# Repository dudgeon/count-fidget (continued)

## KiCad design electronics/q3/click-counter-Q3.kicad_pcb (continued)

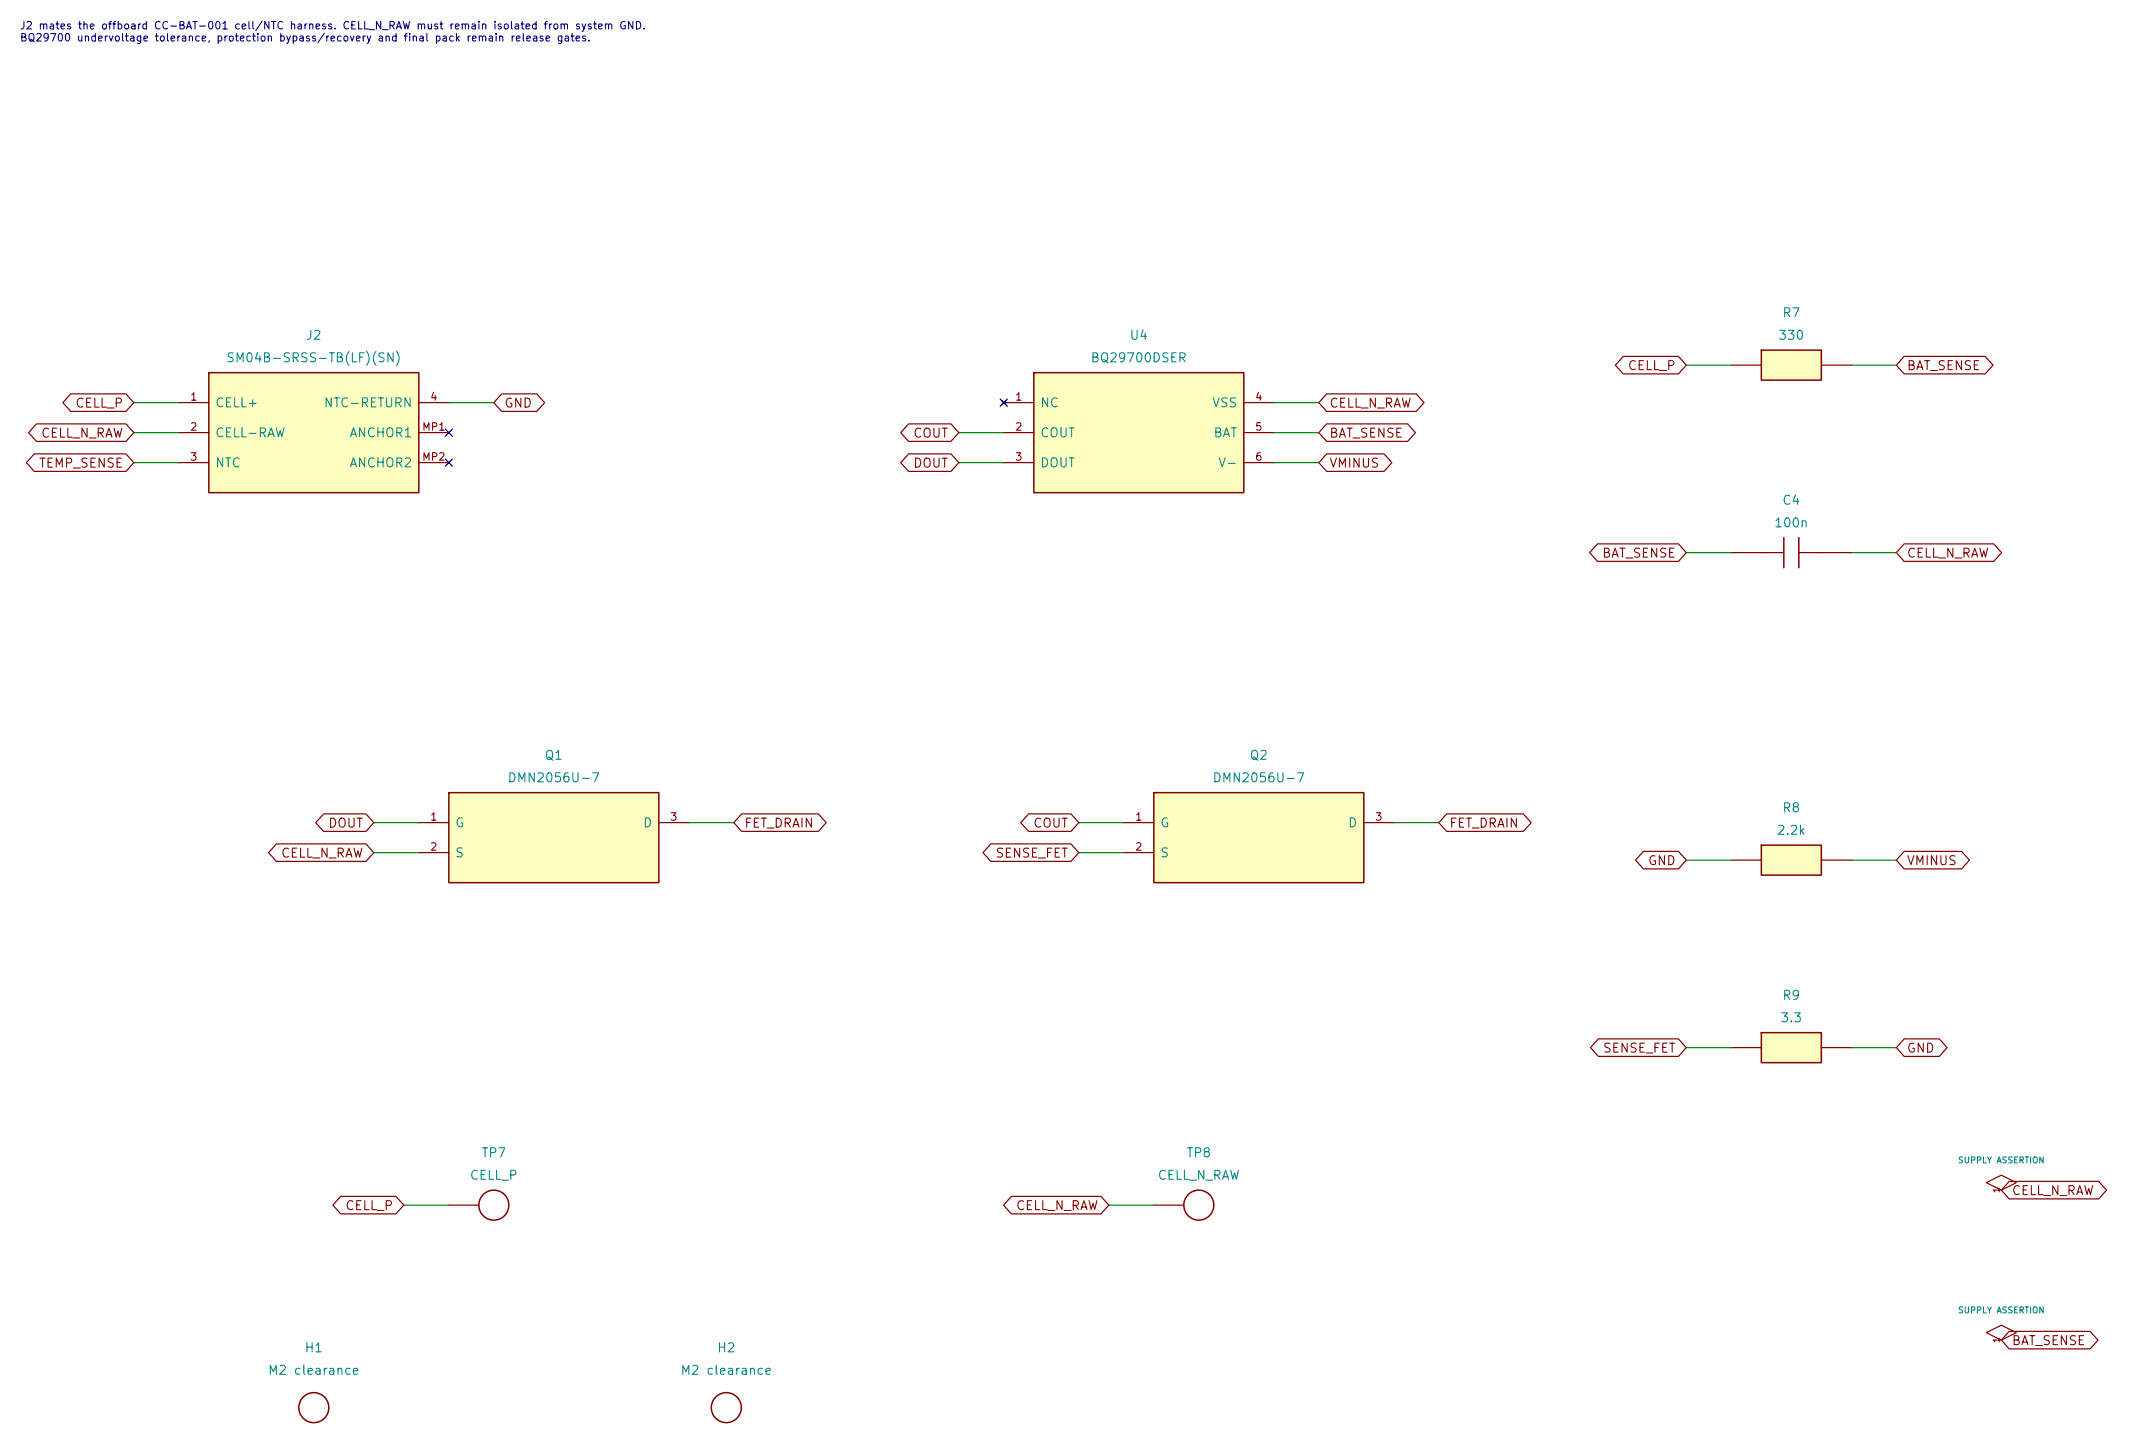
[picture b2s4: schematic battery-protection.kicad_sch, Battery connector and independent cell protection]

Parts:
C4: 100n; Capacitor_SMD_C_0603_1608Metric; MPN GRM188R71H104KA93D
H1, H2: M2 clearance; MountingHole_MountingHole_2.2mm_M2; MPN NPTH
J2: Battery + NTC; Connector_JST_JST_SH_SM04B-SRSS-TB_1x04-1MP_P1.00mm_Horizon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; MPN SM04B-SRSS-TB(LF)(SN)
Q1: Discharge FET; Package_TO_SOT_SMD_SOT-23; MPN DMN2056U-7
Q2: Charge FET; Package_TO_SOT_SMD_SOT-23; MPN DMN2056U-7
R7: 330; Resistor_SMD_R_0603_1608Metric; MPN RC0603FR-07330RL
R8: 2.2k; Resistor_SMD_R_0603_1608Metric; MPN RC0603FR-072K2L
R9: 3.3; Resistor_SMD_R_0603_1608Metric; MPN 0603WAF330KT5E
TP7: CELL_P; TestPoint_TestPoint_Pad_D1.5mm; MPN PCB LAND
TP8: CELL_N_RAW; TestPoint_TestPoint_Pad_D1.5mm; MPN PCB LAND
U4: Cell protector; Package_SON_WSON-6_1.5x1.5mm_P0.5mm; MPN BQ29700DSER

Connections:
BAT_SENSE: C4.1, R7.2, U4.5 (BAT)
CELL_N_RAW: C4.2, J2.2 (CELL-RAW), Q1.2 (S), TP8.1 (1_1), U4.4 (VSS)
CELL_P: J2.1 (CELL+), R7.1, TP7.1 (1_1); also elsewhere on the board
COUT: Q2.1 (G), U4.2 (COUT)
DOUT: Q1.1 (G), U4.3 (DOUT)
FET_DRAIN: Q1.3 (D), Q2.3 (D)
GND: J2.4 (NTC-RETURN), R8.1, R9.2; also elsewhere on the board
SENSE_FET: Q2.2 (S), R9.1
TEMP_SENSE: J2.3 (NTC); also elsewhere on the board
VMINUS: R8.2, U4.6 (V-)

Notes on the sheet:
J2 mates the offboard CC-BAT-001 cell/NTC harness. CELL_N_RAW must remain isolated from system GND. BQ29700 undervoltage tolerance, protection bypass/recovery and final pack remain release gates.

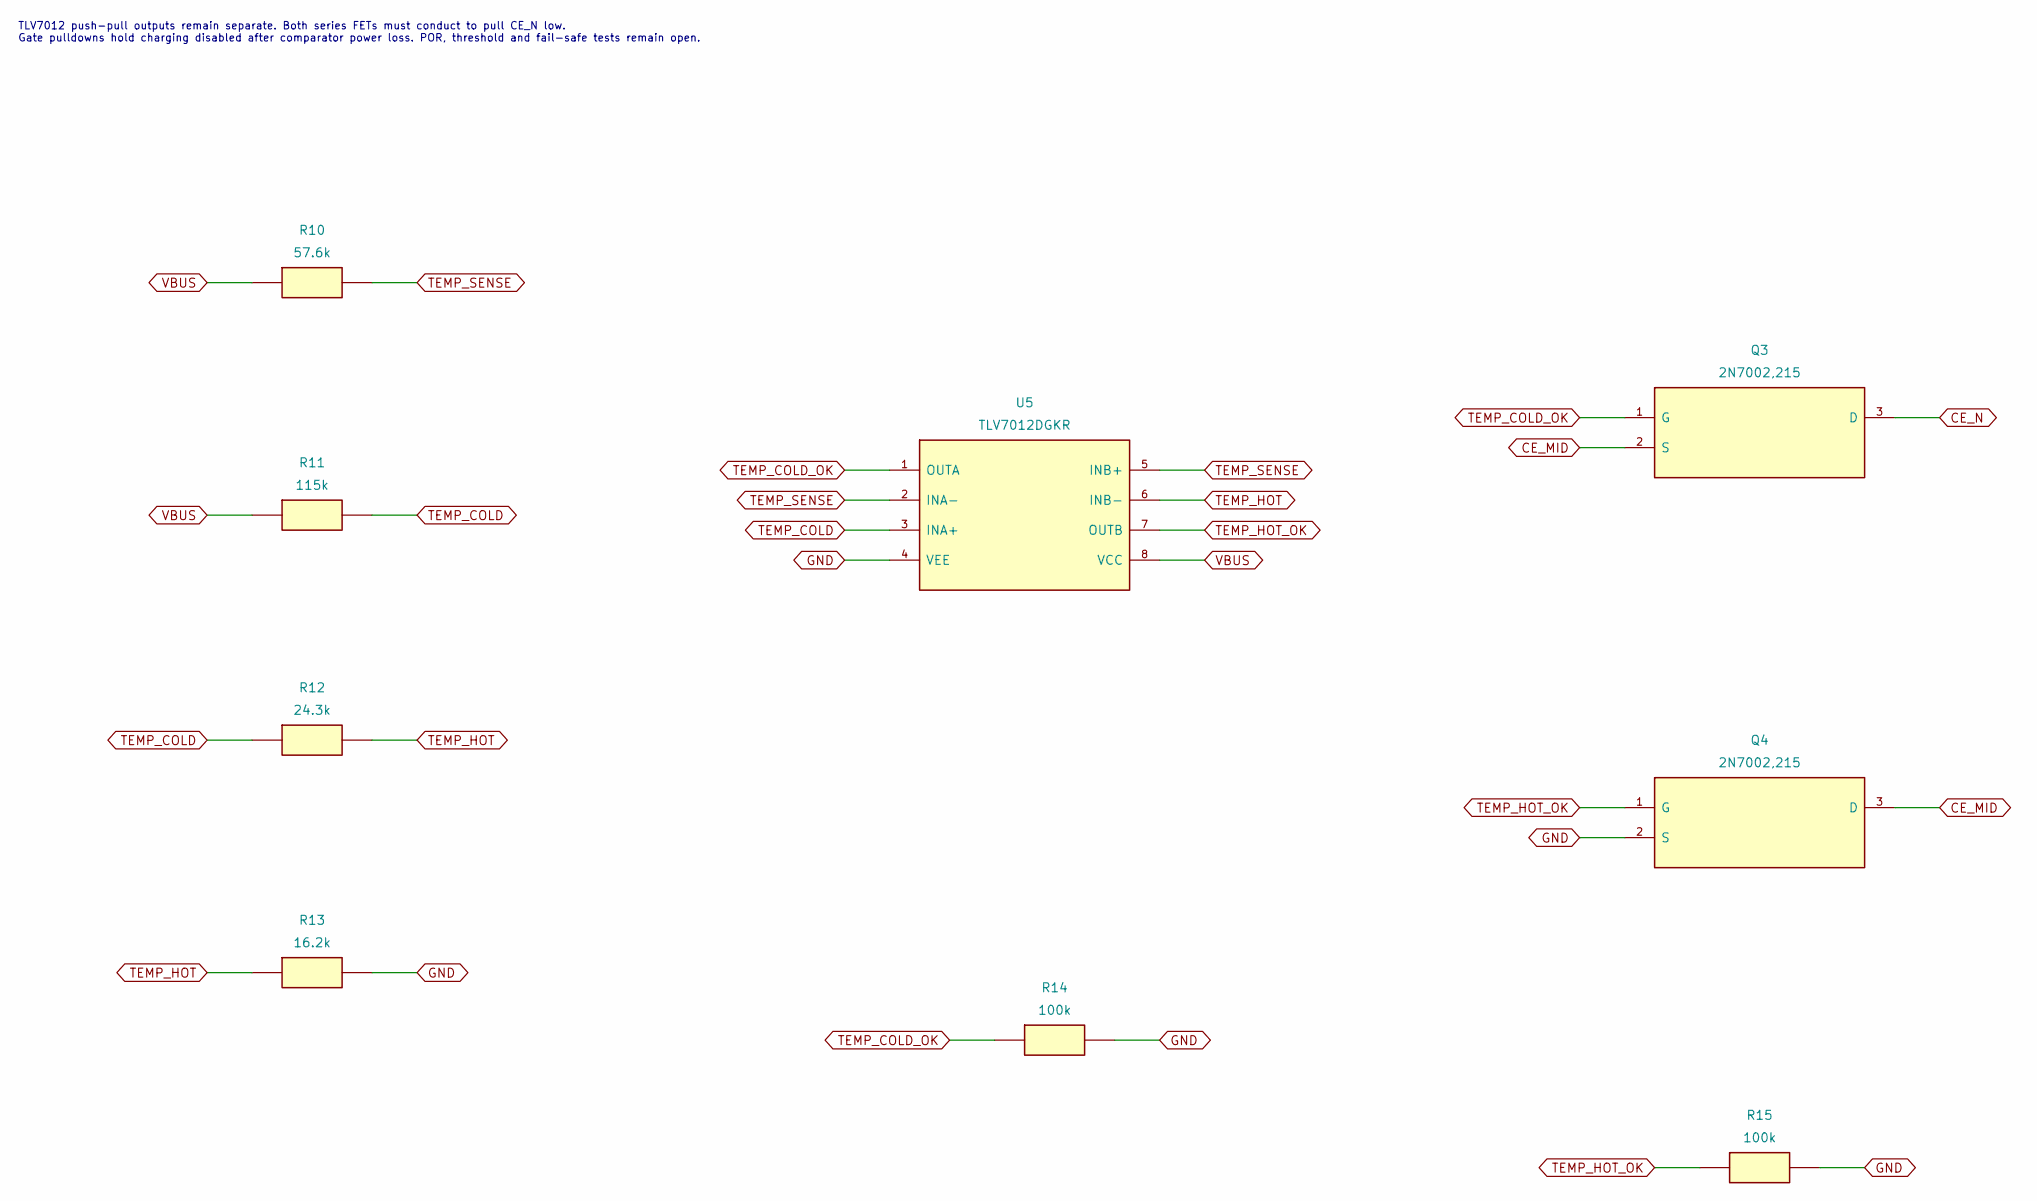
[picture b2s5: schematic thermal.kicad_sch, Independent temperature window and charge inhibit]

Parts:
Q3: Charge enable; Package_TO_SOT_SMD_SOT-23; MPN 2N7002,215
Q4: Charge enable hot gate; Package_TO_SOT_SMD_SOT-23; MPN 2N7002,215
R10: 57.6k; Resistor_SMD_R_0603_1608Metric; MPN RC0603FR-0757K6L
R11: 115k; Resistor_SMD_R_0603_1608Metric; MPN 0603WAF1153T5E
R12: 24.3k; Resistor_SMD_R_0603_1608Metric; MPN RC0603FR-0724K3L
R13: 16.2k; Resistor_SMD_R_0603_1608Metric; MPN RC0603FR-0716K2L
R14, R15: 100k; Resistor_SMD_R_0603_1608Metric; MPN RC0603FR-07100KL
U5: Push-pull temperature window; TLV7032_DGK0008A_TI; MPN TLV7012DGKR

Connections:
CE_MID: Q3.2 (S), Q4.3 (D)
CE_N: Q3.3 (D); also elsewhere on the board
GND: Q4.2 (S), R13.2, R14.2, R15.2, U5.4 (VEE); also elsewhere on the board
TEMP_COLD: R11.2, R12.1, U5.3 (INA+)
TEMP_COLD_OK: Q3.1 (G), R14.1, U5.1 (OUTA)
TEMP_HOT: R12.2, R13.1, U5.6 (INB-)
TEMP_HOT_OK: Q4.1 (G), R15.1, U5.7 (OUTB)
TEMP_SENSE: R10.2, U5.2 (INA-), U5.5 (INB+); also elsewhere on the board
VBUS: R10.1, R11.1, U5.8 (VCC); also elsewhere on the board

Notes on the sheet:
TLV7012 push-pull outputs remain separate. Both series FETs must conduct to pull CE_N low. Gate pulldowns hold charging disabled after comparator power loss. POR, threshold and fail-safe tests remain open.

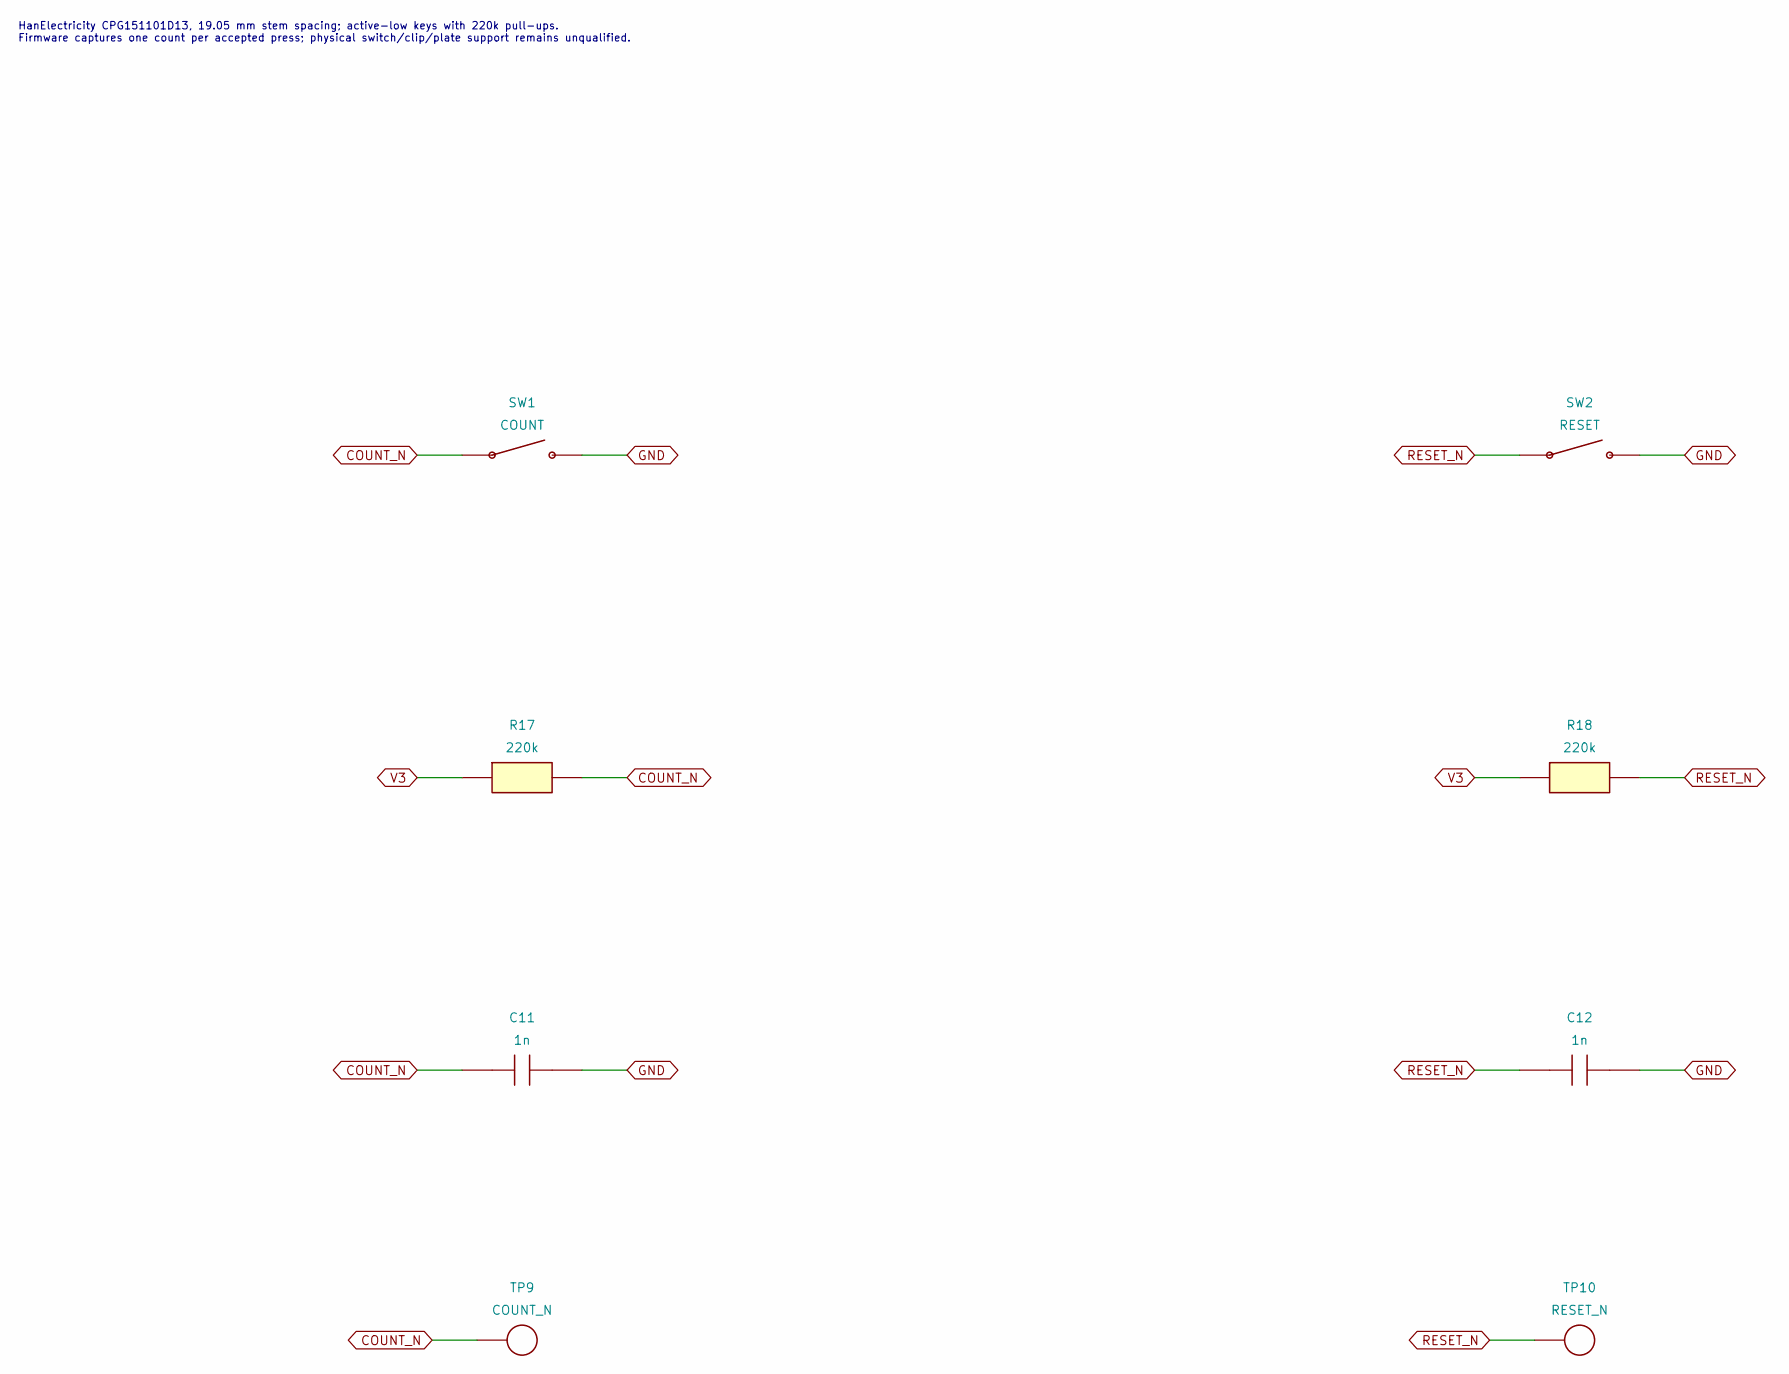
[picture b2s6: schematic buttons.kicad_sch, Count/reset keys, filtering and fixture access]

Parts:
C11, C12: 1n; Capacitor_SMD_C_0603_1608Metric; MPN GRM1885C1H102JA01D
R17, R18: 220k; Resistor_SMD_R_0603_1608Metric; MPN 0603WAF2203T5E
SW1: COUNT; HanElectricity_CPG151101D13_MX_Plate; MPN CPG151101D13
SW2: RESET; HanElectricity_CPG151101D13_MX_Plate; MPN CPG151101D13
TP9: COUNT_N; TestPoint_TestPoint_Pad_D1.5mm; MPN PCB LAND
TP10: RESET_N; TestPoint_TestPoint_Pad_D1.5mm; MPN PCB LAND

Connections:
COUNT_N: C11.1, R17.2, SW1.1, TP9.1 (1_1); also elsewhere on the board
GND: C11.2, C12.2, SW1.2, SW2.2; also elsewhere on the board
RESET_N: C12.1, R18.2, SW2.1, TP10.1 (1_1); also elsewhere on the board
V3: R17.1, R18.1; also elsewhere on the board

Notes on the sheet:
HanElectricity CPG151101D13, 19.05 mm stem spacing; active-low keys with 220k pull-ups. Firmware captures one count per accepted press; physical switch/clip/plate support remains unqualified.

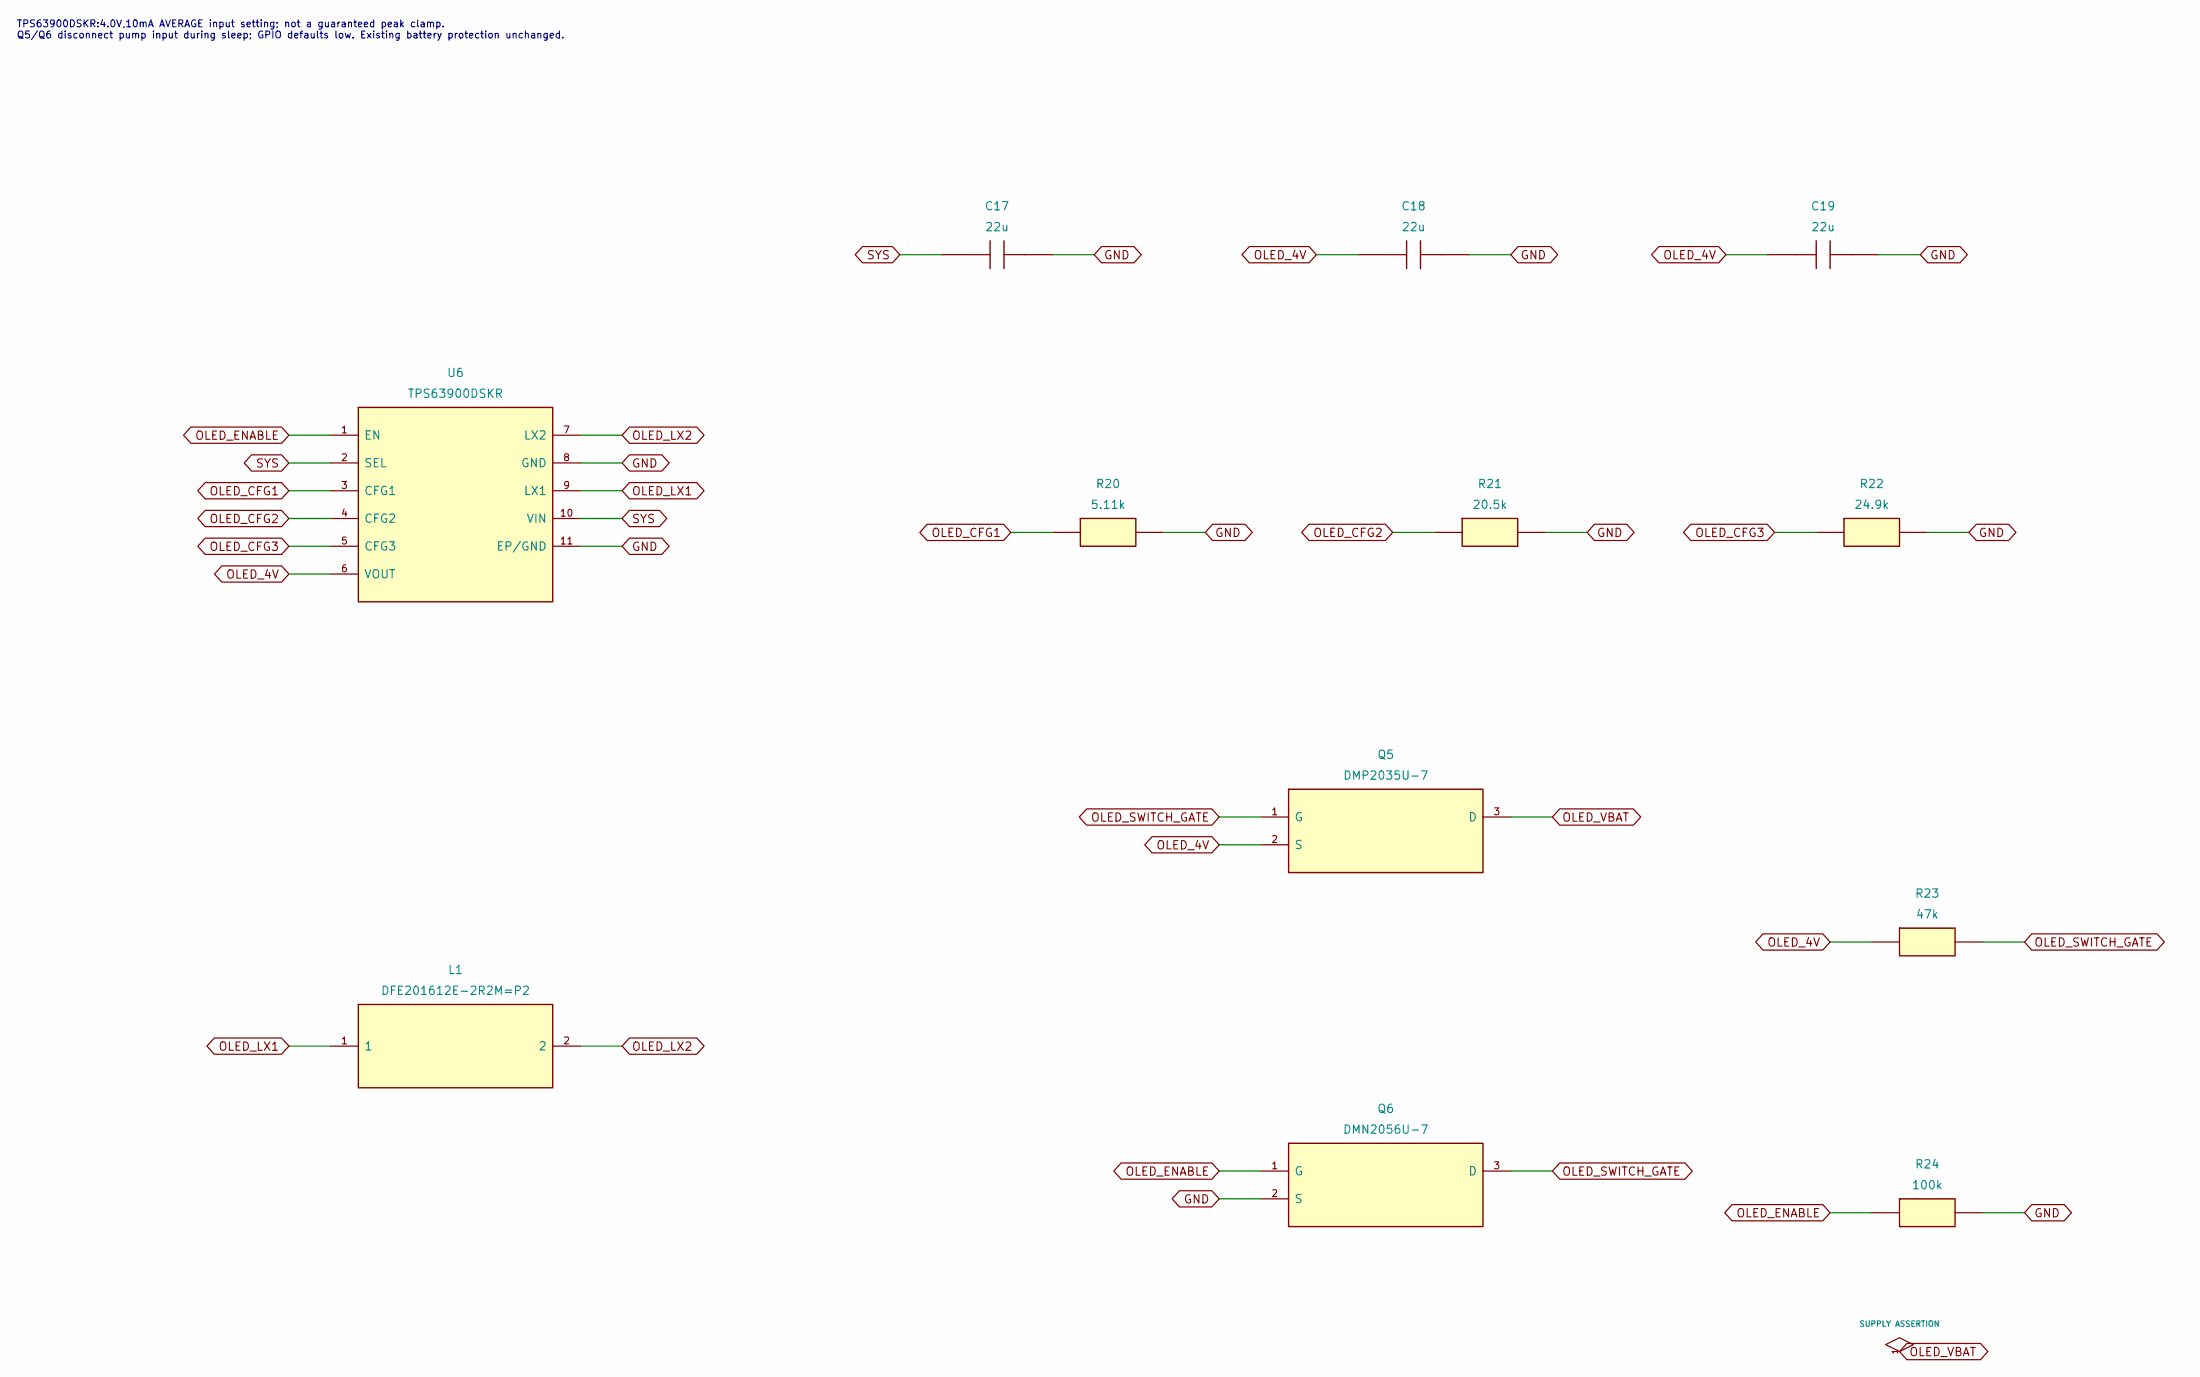
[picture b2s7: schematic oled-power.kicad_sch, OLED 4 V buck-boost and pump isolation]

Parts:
C17, C18, C19: 22u; Capacitor_SMD_C_0805_2012Metric; MPN CL21A226MAYNNNE
L1: 2.2u; Inductor_SMD_L_Murata_DFE201612E_2.0x1.6mm; MPN DFE201612E-2R2M=P2
Q5: OLED VBAT disconnect; Package_TO_SOT_SMD_SOT-23; MPN DMP2035U-7
Q6: OLED switch gate; Package_TO_SOT_SMD_SOT-23; MPN DMN2056U-7
R20: 5.11k; Resistor_SMD_R_0603_1608Metric; MPN RC0603FR-075K11L
R21: 20.5k; Resistor_SMD_R_0603_1608Metric; MPN RC0603FR-0720K5L
R22: 24.9k; Resistor_SMD_R_0603_1608Metric; MPN RC0603FR-0724K9L
R23: 47k; Resistor_SMD_R_0603_1608Metric; MPN 0603WAF4702T5E
R24: 100k; Resistor_SMD_R_0603_1608Metric; MPN RC0603FR-07100KL
U6: 4.0V OLED buck-boost; TPS63900_DSK0010A_TI; MPN TPS63900DSKR

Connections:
GND: C17.2, C18.2, C19.2, Q6.2 (S), R20.2, R21.2, R22.2, R24.2, U6.8 (GND), U6.11 (EP/GND); also elsewhere on the board
OLED_4V: C18.1, C19.1, Q5.2 (S), R23.1, U6.6 (VOUT)
OLED_CFG1: R20.1, U6.3 (CFG1)
OLED_CFG2: R21.1, U6.4 (CFG2)
OLED_CFG3: R22.1, U6.5 (CFG3)
OLED_ENABLE: Q6.1 (G), R24.1, U6.1 (EN); also elsewhere on the board
OLED_LX1: L1.1, U6.9 (LX1)
OLED_LX2: L1.2, U6.7 (LX2)
OLED_SWITCH_GATE: Q5.1 (G), Q6.3 (D), R23.2
OLED_VBAT: Q5.3 (D); also elsewhere on the board
SYS: C17.1, U6.2 (SEL), U6.10 (VIN); also elsewhere on the board

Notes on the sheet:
TPS63900DSKR:4.0V,10mA AVERAGE input setting; not a guaranteed peak clamp. Q5/Q6 disconnect pump input during sleep; GPIO defaults low. Existing battery protection unchanged.

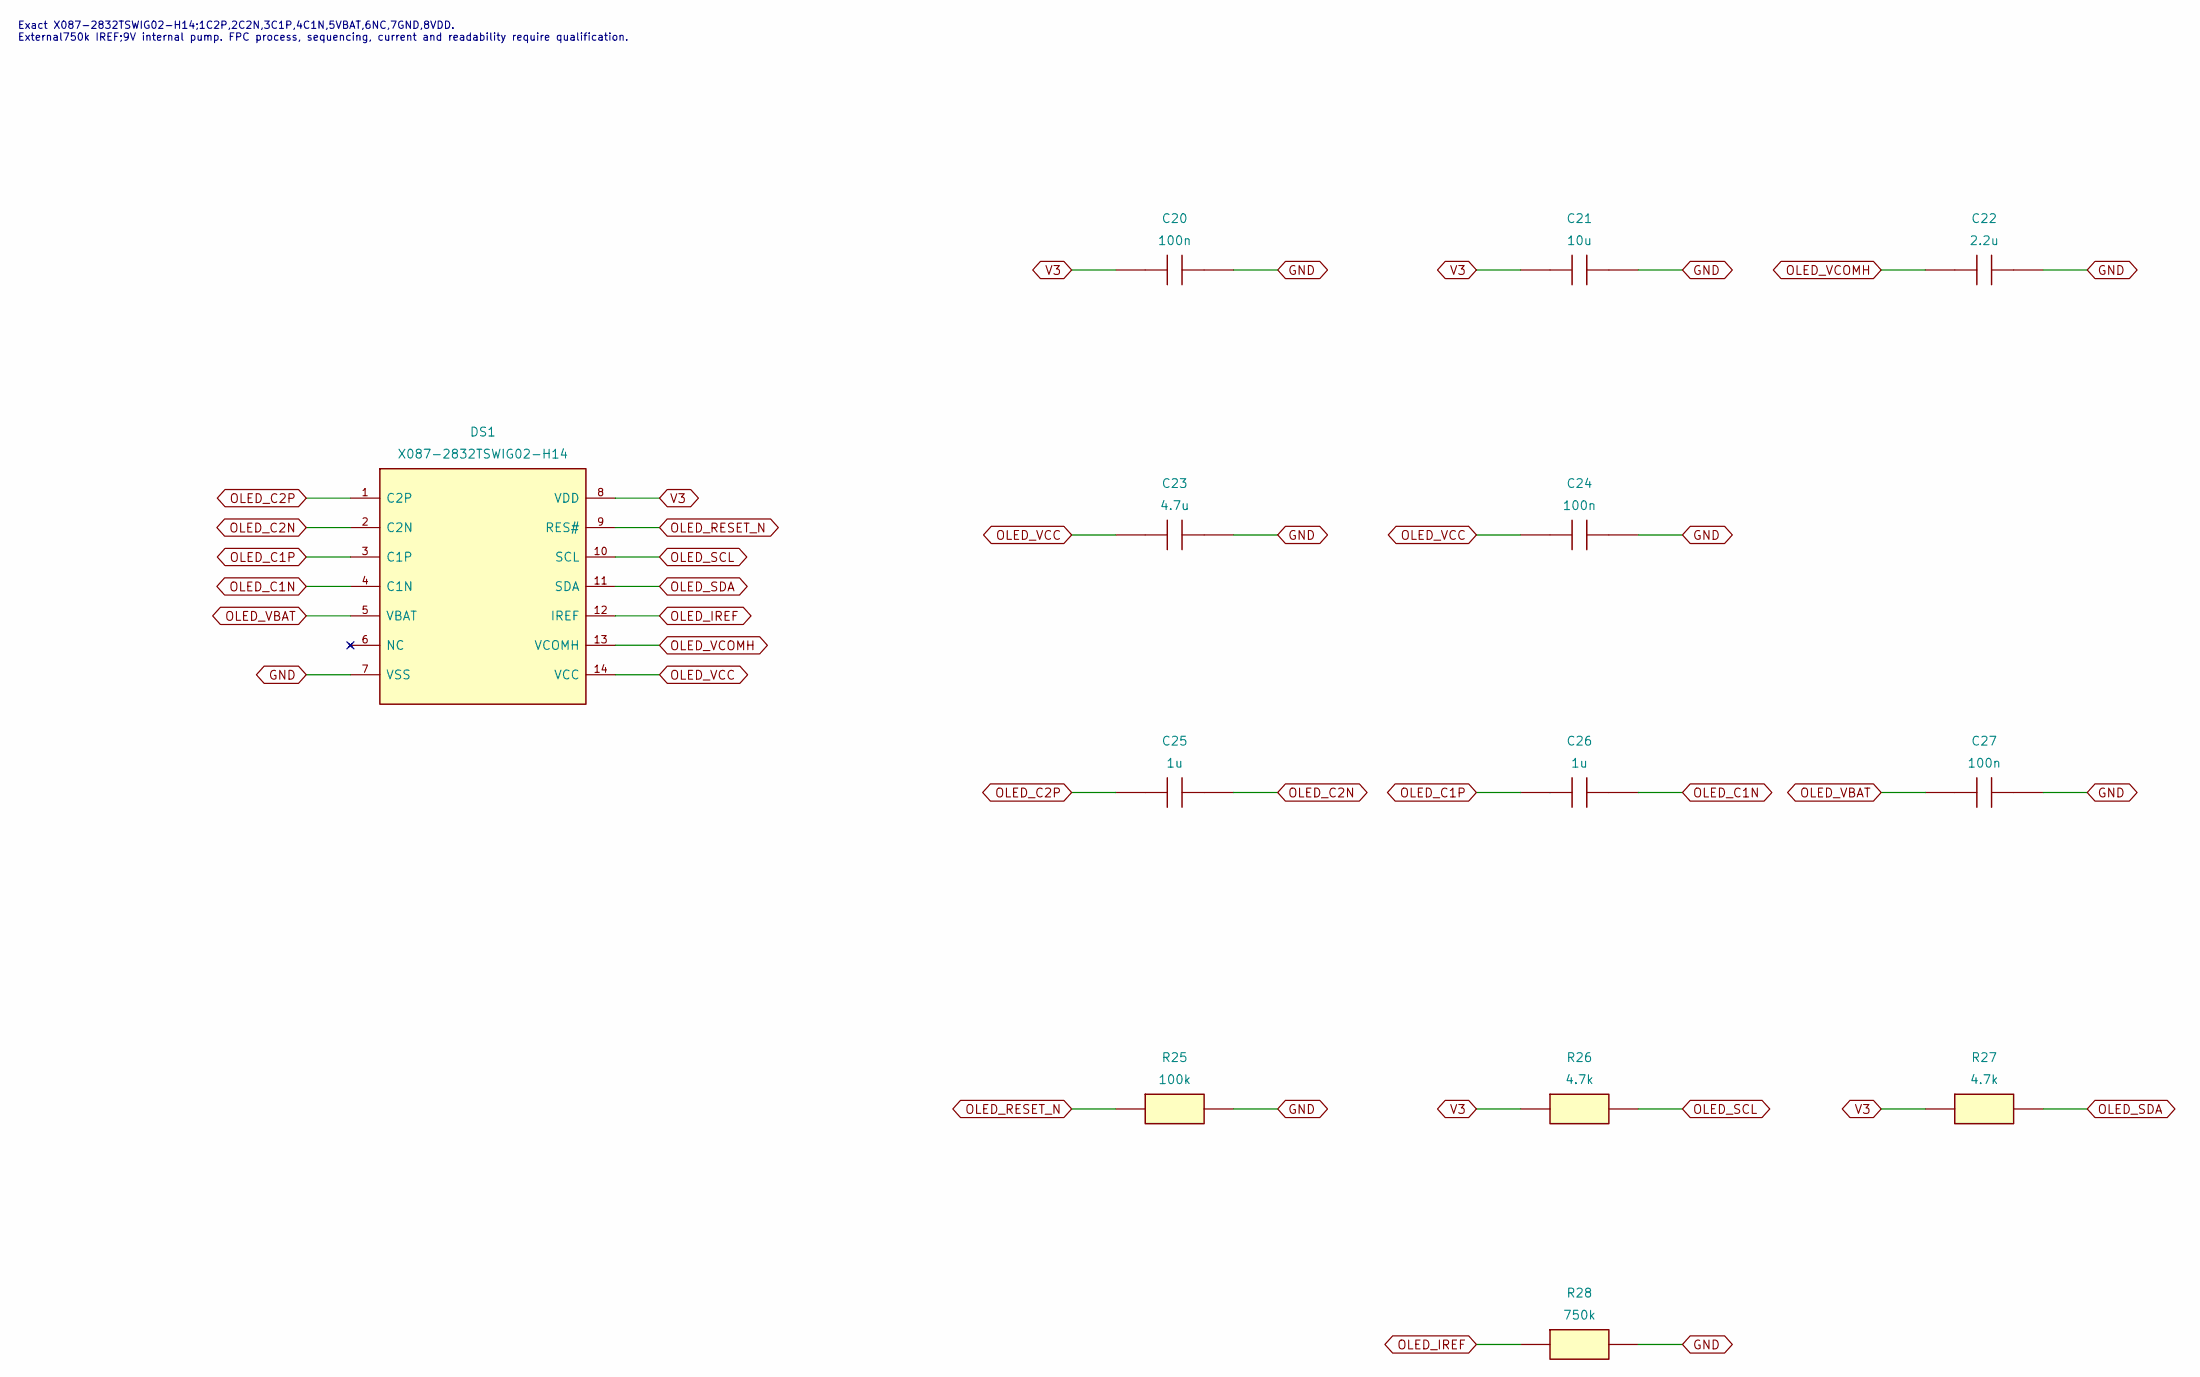
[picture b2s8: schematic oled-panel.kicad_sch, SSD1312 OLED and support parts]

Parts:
C20, C24, C27: 100n; Capacitor_SMD_C_0603_1608Metric; MPN GRM188R71H104KA93D
C21: 10u; Capacitor_SMD_C_0805_2012Metric; MPN GRM21BR61E106KA73L
C22: 2.2u; Capacitor_SMD_C_0805_2012Metric; MPN GRM21BR71E225KE11L
C23: 4.7u; Capacitor_SMD_C_0805_2012Metric; MPN GRM21BZ71H475KE15L
C25, C26: 1u; Capacitor_SMD_C_0603_1608Metric; MPN CL10B105KA8NNNC
DS1: X087-2832TSWIG02-H14; MPN X087-2832TSWIG02-H14
R25: 100k; Resistor_SMD_R_0603_1608Metric; MPN RC0603FR-07100KL
R26, R27: 4.7k; Resistor_SMD_R_0603_1608Metric; MPN RC0603FR-074K7L
R28: 750k; Resistor_SMD_R_0603_1608Metric; MPN RC0603FR-07750KL

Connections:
GND: C20.2, C21.2, C22.2, C23.2, C24.2, C27.2, DS1.7 (VSS), R25.2, R28.2; also elsewhere on the board
OLED_C1N: C26.2, DS1.4 (C1N)
OLED_C1P: C26.1, DS1.3 (C1P)
OLED_C2N: C25.2, DS1.2 (C2N)
OLED_C2P: C25.1, DS1.1 (C2P)
OLED_IREF: DS1.12 (IREF), R28.1
OLED_RESET_N: DS1.9 (RES#), R25.1; also elsewhere on the board
OLED_SCL: DS1.10 (SCL), R26.2; also elsewhere on the board
OLED_SDA: DS1.11 (SDA), R27.2; also elsewhere on the board
OLED_VBAT: C27.1, DS1.5 (VBAT); also elsewhere on the board
OLED_VCC: C23.1, C24.1, DS1.14 (VCC)
OLED_VCOMH: C22.1, DS1.13 (VCOMH)
V3: C20.1, C21.1, DS1.8 (VDD), R26.1, R27.1; also elsewhere on the board

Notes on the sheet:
Exact X087-2832TSWIG02-H14;1C2P,2C2N,3C1P,4C1N,5VBAT,6NC,7GND,8VDD. External750k IREF;9V internal pump. FPC process, sequencing, current and readability require qualification.

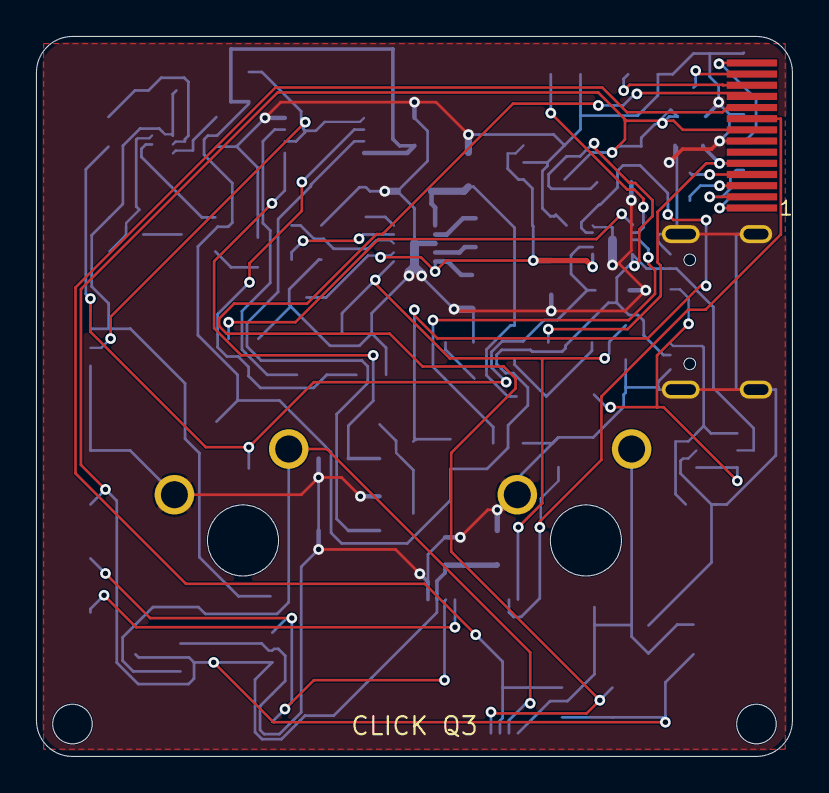
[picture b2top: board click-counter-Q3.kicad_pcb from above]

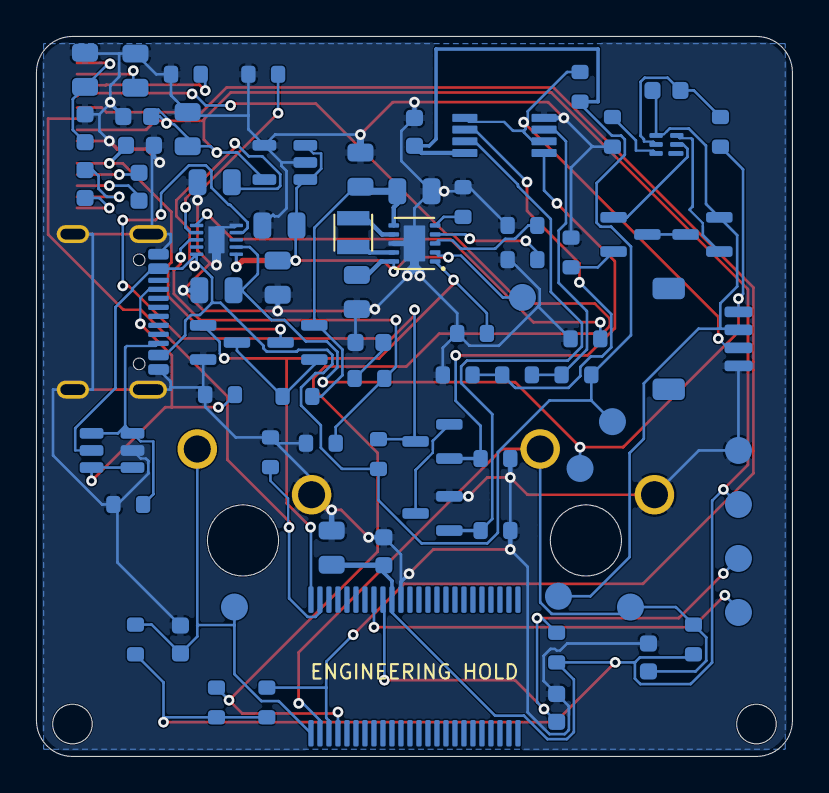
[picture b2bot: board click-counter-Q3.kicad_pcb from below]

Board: 2 copper layers, 42.0 x 40.0 mm, 82 parts (77 on the bottom side), 48 nets.
